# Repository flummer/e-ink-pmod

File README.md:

# E-Ink PMOD with SRAM

## Features

- Simple PMOD form factor breakout board with the required components to drive an e-ink display from regular 3.3v electronics
- There is also an SRAM chip (23K640-I/SN) on board, eg. for use as a frame buffer

## Source files in KiCad v9

To open the project, you will need to install KiCad v9 or a nightly build. KiCad v8 or earlier won't open this design directly. Earlier commits will be saved in a previous version.

[Electronics schematics as a PDF file](https://github.com/flummer/e-ink-pmod/blob/main/schematic.pdf) is also included for reference.

[Design can also be viewed in the KiCanvas online viewer](https://kicanvas.org/?github=https%3A%2F%2Fgithub.com%2Fflummer%2Fe-ink-pmod)

## License

The hardware design in this repository is released under the following license:

* the "Creative Commons Attribution-ShareAlike 4.0 International License"
  (CC BY-SA 4.0) full text of this license is included in the LICENSE file
  and a copy can also be found at
  [http://creativecommons.org/licenses/by-sa/4.0/](http://creativecommons.org/licenses/by-sa/4.0/)

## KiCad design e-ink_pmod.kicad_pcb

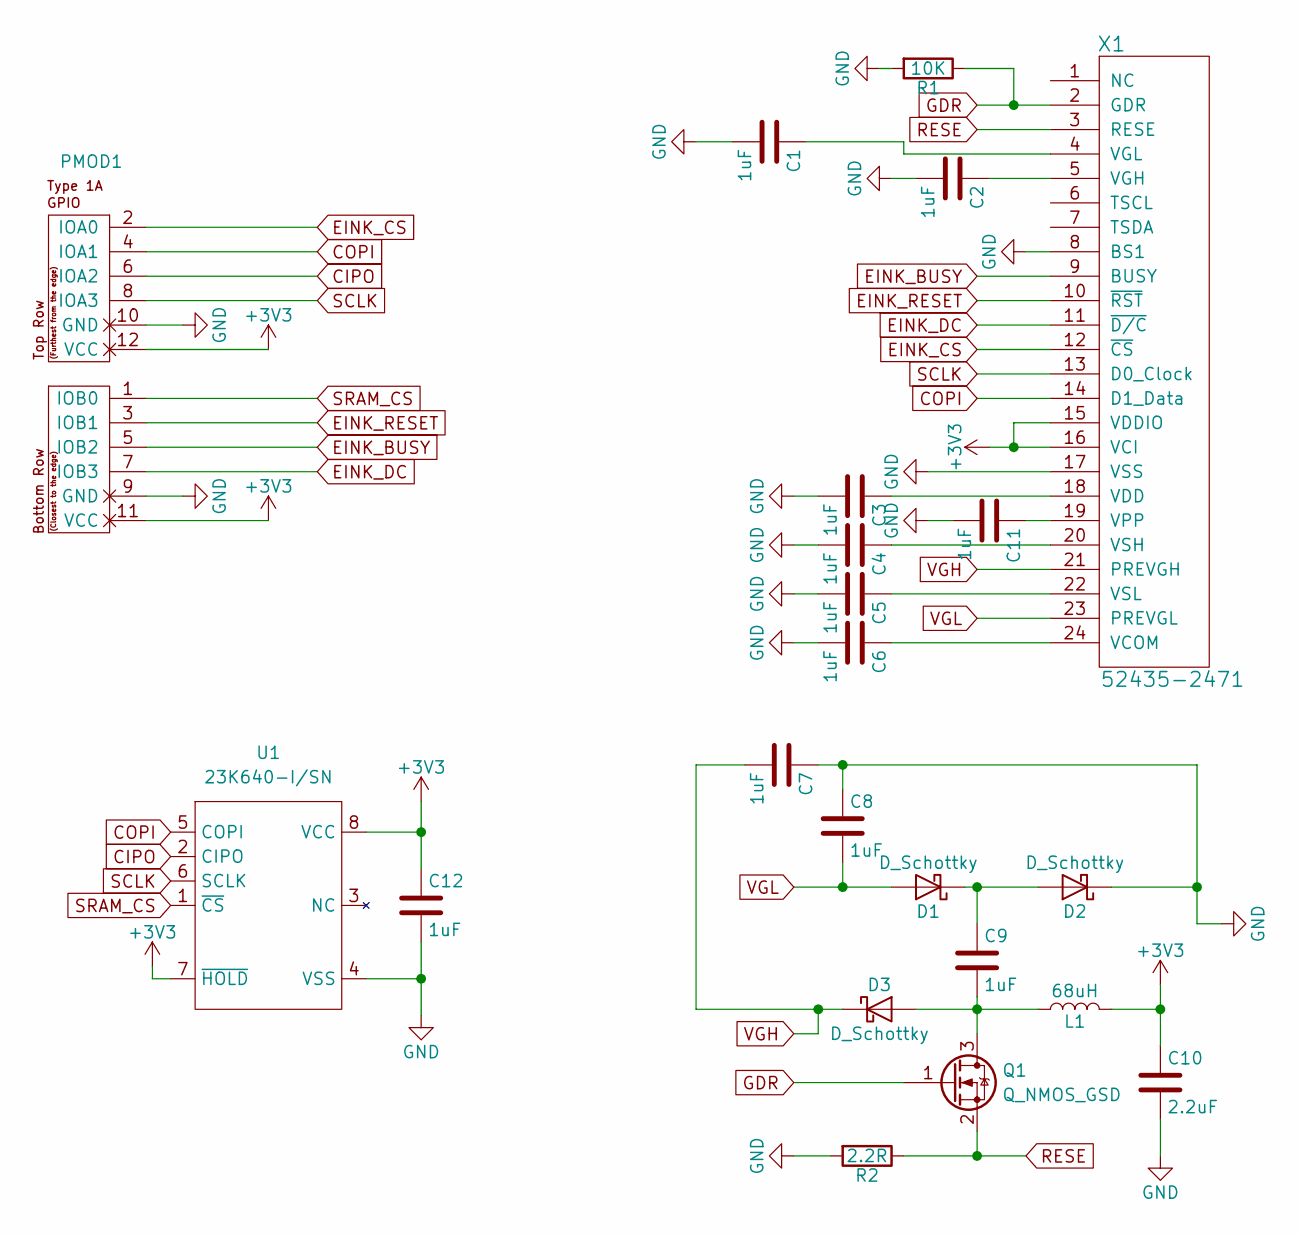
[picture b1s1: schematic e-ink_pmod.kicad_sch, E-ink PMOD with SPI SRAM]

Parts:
C1, C2, C3, C4, C5, C6, C7, C8, C9, C11, C12: 1uF; C_0805_2012Metric
C10: 2.2uF; C_0805_2012Metric
D1, D2, D3: D_Schottky; D_SOD-123
L1: 68uH; L_1812_4532Metric
PMOD1: QMOD-Device-x2-Type-1A-GPIO; pmod_pin_array_6x2
Q1: Q_NMOS_GSD; SOT-23
R1: 10K; R_0805_2012Metric
R2: 2.2R; R_0805_2012Metric
U1: 23K640-I/SN; SOIC-8_3.9x4.9mm_P1.27mm
X1: 52435-2471; MOLEX_52435-2471

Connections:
+3V3: C10.1, C12.1, L1.2, PMOD1.11 (VCC), PMOD1.12 (VCC), U1.7 (~HOLD), U1.8 (VCC), X1.15 (VDDIO), X1.16 (VCI); also elsewhere on the board
CIPO: PMOD1.6 (IOA2), U1.2 (CIPO); also elsewhere on the board
COPI: PMOD1.4 (IOA1), U1.5 (COPI), X1.14 (D1_Data); also elsewhere on the board
EINK_BUSY: PMOD1.5 (IOB2), X1.9 (BUSY); also elsewhere on the board
EINK_CS: PMOD1.2 (IOA0), X1.12 (~CS); also elsewhere on the board
EINK_DC: PMOD1.7 (IOB3), X1.11 (~D/C); also elsewhere on the board
EINK_RESET: PMOD1.3 (IOB1), X1.10 (~RST); also elsewhere on the board
GDR: Q1.1 (G), R1.1, X1.2 (GDR)
GND: C1.2, C2.2, C3.2, C4.2, C5.2, C6.2, C7.1, C8.1, C10.2, C11.2, C12.2, D2.1 (K), PMOD1.9 (GND), PMOD1.10 (GND), R1.2, R2.2, U1.4 (VSS), X1.8 (BS1), X1.17 (VSS); also elsewhere on the board
unnamed: C1.1, X1.4 (VGL)
unnamed: C2.1, X1.5 (VGH)
unnamed: C3.1, X1.18 (VDD)
unnamed: C4.1, X1.20 (VSH)
unnamed: C5.1, X1.22 (VSL)
unnamed: C6.1, X1.24 (VCOM)
unnamed: C9.1, D1.1 (K), D2.2 (A)
unnamed: C9.2, D3.2 (A), L1.1, Q1.3 (D)
unnamed: C11.1, X1.19 (VPP)
RESE: Q1.2 (S), R2.1, X1.3 (RESE)
SCLK: PMOD1.8 (IOA3), U1.6 (SCLK), X1.13 (D0_Clock); also elsewhere on the board
SRAM_CS: PMOD1.1 (IOB0), U1.1 (~CS); also elsewhere on the board
VGH: C7.2, D3.1 (K), X1.21 (PREVGH)
VGL: C8.2, D1.2 (A), X1.23 (PREVGL)

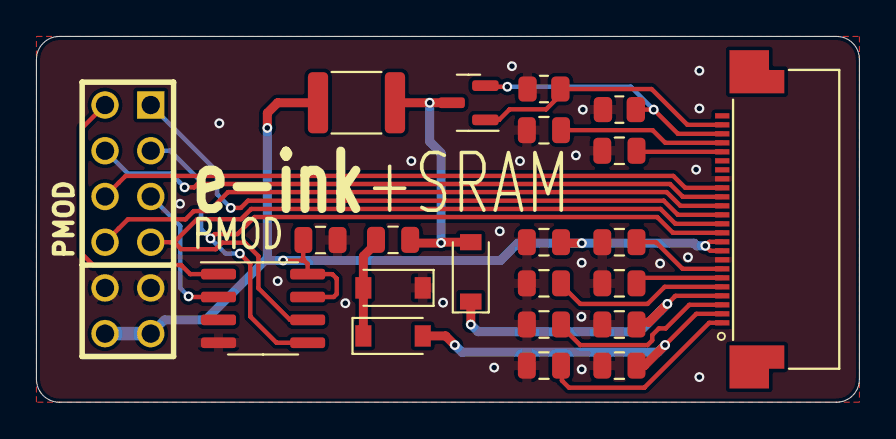
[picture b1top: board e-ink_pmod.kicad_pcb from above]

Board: 2 copper layers, 45.7 x 20.3 mm, 22 parts (0 on the bottom side), 23 nets.

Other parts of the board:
PMOD: QMOD-Device-x2-Type-1A-GPIO; pmod_pin_array_6x2

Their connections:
+3V3: PMOD.11 (VCC), PMOD.12 (VCC); also elsewhere on the board
CIPO: PMOD.6 (IOA2); also elsewhere on the board
COPI: PMOD.4 (IOA1); also elsewhere on the board
EINK_BUSY: PMOD.5 (IOB2); also elsewhere on the board
EINK_CS: PMOD.2 (IOA0); also elsewhere on the board
EINK_DC: PMOD.7 (IOB3); also elsewhere on the board
EINK_RESET: PMOD.3 (IOB1); also elsewhere on the board
GND: PMOD.9 (GND), PMOD.10 (GND); also elsewhere on the board
SCLK: PMOD.8 (IOA3); also elsewhere on the board
SRAM_CS: PMOD.1 (IOB0); also elsewhere on the board

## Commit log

2021-01-03 Added SPI SRAM for framebuffer
    Also updated to new KiCad version 6 file formats
2021-01-07 Fixed dimension and changed display unit
2025-05-06 Updated documentation
    Also updated KiCad version for better compatibility with KiCanvas
